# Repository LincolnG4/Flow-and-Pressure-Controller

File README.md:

# Protótipo de controle de fluxo de massa e leitura de pressão

O objetivo principal deste trabalho é desenvolver um protótipo de um sistema, composto de _hardware_, _firmware_ e _software_, para controle do fluxo e pressão de gases durante tratamento de materiais.

Os objetivos :

- Desenvolver um protótipo de um sistema de controle e alimentação de 4 _MFC_ MKS 500 _SCCM_ e leitura de pressão através de 1 Pirani APGX-M-NW16/ALI Edwards;

-  Desenvolver modos de funcionamento programados, tais como: liga/desliga de coleta sensores, pre-sets de gases comuns e alerta de erro;
- Desenvolver a placa de circuito impresso;
- Desenvolver a coleta de dados dos sensores.

## Wish list
Lista de desejos para o futuro do projeto:  
- [ ] Estudo mais detalhado dos resultados dos sinais aplicando metrologia; _`Em desenvolvimento`_
- [ ]  Sofware em Python para concatenar e gerar um grafico interativo; _`Em desenvolvimento`_
- [ ] Utilização de um hardware com Wi-Fi embutido e com mais de um núcleo, assim, permitindo multitarefas;
- [ ] Utilização de um processador de fácil integração na placa PCB;
- [ ] Otimização da programação; _`Em desenvolvimento`_
- [ ] Garantir a não utilização de um hardware genérico;
- [ ] Utilização de um roteador de internet dentro do laboratório;
- [ ] Remodelar o case para montagem por encaixe clicáveis ao invés de parafusos; _`Em desenvolvimento`_
- [ ] Função para alteração de data e hora do RTC; _`Em desenvolvimento`_

# 1. Visão Geral

 - Fonte de alimentação: 24 V ( **O módulo Step-Down aceita até 40 V de entrada, porém é necessário desmonta-lo e regular através do parafuso a saída para 7V** )
 - Sinal de saída: 0-5 V
 - Dimensões: 165,5 x 74,6 x 41 mm
 - Tela: Nextion Touch 320x240
 - Armazenamento: cartão microSD até 64 GB e 15GB em nuvem
 - Portas: 4 entradas DB9-macho, 1 entrada RJ45-femea e uma porta usb (debug)

## 1.1 Componentes

| Componente | Unidade | Preço/unidade (R$) | Total | Link | 
|--|--|--|--|--|
|Arduino Mega|1| 200,00 | 200,00  | [Compre](https://www.baudaeletronica.com.br/arduino-mega-2560-compativel-cabo-usb.html) |
| Capacitor 1uF |9| 0,23 | 2,07 | [Compre](https://www.eletrogate.com/capacitor-eletrolitico-1uf-x-50v ) |
| Conector DB9|4|3,00  | 12,00 |  [Compre](https://www.soldafria.com.br/conector-db9-macho-90-graus-solda-placa-p-1709.html) |
| Conector RJ45 |1|4,00 | 4,00  |  |
| Conector Alimentação|1| 2,50 | 2,50  | [Compre](https://www.robocore.net/conector/conector-dc-p4-femea)  |
| Fonte de alimentação 24V |1| 30,00 | 30,00 |  |
| Modulo Leitor de microSD | 1 | 12,00 | 12,00 | [Compre](https://www.eletrogate.com/modulo-micro-sd-card)  |
| Modulo LM2596 StepDown | 1 |15,00  | 15,00  | [Compre](https://www.filipeflop.com/produto/regulador-de-tensao-lm2596-conversor-dc-dc-step-down/) |
| Modulo WiFi ESP8266 |1| 20,00 | 20,00  | [Compre](https://www.eletrogate.com/modulo-wifi-serial-esp8266-esp-01) |
| Resistor 4.7k Ohms |6|0,05| 0,30 | [Compre](https://www.eletrogate.com/resistor-4k7-1-4w-10-unidades ) |
| Resistor 470 Ohms |8| 0,05 |0,40 |[Compre](https://www.eletrogate.com/resistor-4k7-1-4w-10-unidades )  |
| Resistor 220 Ohms |1| 0,05 | 0,05  |[Compre](https://www.eletrogate.com/resistor-4k7-1-4w-10-unidades ) |
| RTC 1302 | 1 | 10,00 |10,00 | [Compre](https://www.eletrogate.com/modulo-real-time-clock-ds1302) |
| Tela Nextion 320x240 |1| 120,00 |120,00  | [Compre](https://pt.aliexpress.com/item/32685352949.html?spm=a2g0o.productlist.0.0.10a12308w7t6Pf&algo_pvid=ee404ca7-f5a8-4c20-a123-40767543fb84&algo_exp_id=ee404ca7-f5a8-4c20-a123-40767543fb84-0&pdp_ext_f=%7B%22sku_id%22%3A%2260390805771%22%7D&pdp_npi=2%40dis%21BRL%21%21102.36%21%21%2133.26%21%21%402101d4a716547459631704164eff88%2160390805771%21sea)|
| Transistor BC337 |4| 0,27 | 1,08 | [Compre](https://www.eletrogate.com/ecfjb2rzm-transistor-npn-bc337)  |
| __TOTAL__ ||  |  __544,40__|  |

## 1.2 Tabela de fatores de correção dos gases

Faça o download da tabela de fatores de coreção dos gases em  [DOWNLOAD](https://github.com/LincolnG4/Flow-and-Pressure-Controller/blob/main/gasfactor.xlsx)

## 1.3 FAQ & Troubleshooting

> **A tela do produto está funcionando mas ele não retorna nenhum valor de medição**

- Certifique-se que os conectores da tela estão soldados corretamente 
- Conecte o Arduino na porta USB do seu computador e siga os passos  do tópico `3.3.1.1`
- Certifique-se que não aparecerá nenhuma mensagem de erro no monitor

# 2. Software Utilizados

| SOFTWARE        | DESCRIÇÃO|DOWNLOAD |
|----------------|-------------------------------|-------------------------------|
|`Cura3D`|Software para impressão 3D|https://ultimaker.com/software/ultimaker-cura|
|`FreeCAD 0.19`|CAD|https://www.freecadweb.org/downloads.php	|
|`Kicad 6.0`|Eletrônica e PCB |https://www.kicad.org/download/|
|`Nextion Editor`|Edição da interface LCD|https://nextion.tech/nextion-editor/|
|`Photopea`|Edição de fotos|https://photopea.com/|
|`Schematic editor`|Auto routing para trilha PCB|https://layouteditor.com/download|
|`Visual Studio Code e/ou Arduino IDE`|Edição de codigos|https://code.visualstudio.com / https://www.arduino.cc/en/software/download|

## 2.2 Links úteis 
[Basico do Arduino](https://www.if.ufrj.br/~gpenello/DisciplinasAntigas/Lab2_2018-1/GUIA_ARDUINO_v.2.pdf)
[Básico de Linguagem C++](https://www.inf.ufpr.br/ci208/NotasAula.pdf)
[Básico Cura 3D](https://3dlab.com.br/cura-3d-ultimaker/)
[FreeCAD -> SolidWorks / SolidWorks -> FreeCAD](https://forum.freecadweb.org/viewtopic.php?style=4&t=20778)

# 3. Passo a Passo de construção e instalação
## 3.1 Impressão do  case 3D

Faça o download dos arquivos para impressão 3D:
- [Gabinete](https://github.com/LincolnG4/Flow-and-Pressure-Controller/blob/main/Hardware/CAD/case_bottom-Body.stl)
- [Tampa](https://github.com/LincolnG4/Flow-and-Pressure-Controller/blob/main/Hardware/CAD/case_top-Body.stl)

Recomendações:

- Materiais: PLA ou ABS;
- Confira a [tabela de temperatura](https://3dlab.com.br/temperatura-na-impressao-3d/) para o bico para cada material;
- Configuração através do software [Cura 3D](#software-utilizados):  

## 3.2 Configurando seu ambiente de programação
 Faça o download das bibliotecas a seguir e siga o passo a passo para configuração do seu ambiente de desenvolvimento.
 
### 3.2.1 Bibliotecas Externas Utilizadas 

#### Arduino 

Versão da placa: Arduino AVR Boards 1.8.3
| SOFTWARE        | DESCRIÇÃO|DOWNLOAD |
|----------------|-------------------------------|-------------------------------|
|`ITEADLIB Arduino`|Auxiliar no controle da tela LCD|https://github.com/itead/ITEADLIB_Arduino_Nextion|
|`ArduinoRTClibrary`|Controle do modulo RTC|https://github.com/chrisfryer78/ArduinoRTClibrary|
|`Timelib`|Manipulação time string|https://github.com/PaulStoffregen/Time|
|`UnixTime`|Manipulação de timestamp|https://github.com/GyverLibs/UnixTime|
_______

#### ESP01 

Versão da placa: esp8266 2.4.3
| SOFTWARE        | DESCRIÇÃO|DOWNLOAD |
|----------------|-------------------------------|-------------------------------|
|`WiFi Manager`|Auxiliar no controle do WiFi|https://github.com/tzapu/WiFiManager|

### 3.2.2 Como instalar uma biblioteca 

 1. Abra o link para o donwload da biblioteca (ex: `https://github.com/itead/ITEADLIB_Arduino_Nextion`) e faça o download do `.ZIP`  
 
2. Abra o `Arduino IDE` e vá em `Sketch`>`Incluir biblioteca`> `Adicionar biblioteca .ZIP`  

3. Selecione a biblioteca que você fez o download no Passo 1 

### 3.2.3 Como instalar os gerenciador de placa 

#### Arduino 

1. Abra o `Arduino IDE` e clique em `Ferramentas`>`Placa`>`Gerenciador de placas`  

2. Procure pela placa `Arduino AVR Boards` e selecione a versão `1.8.3`  
_______
#### ESP01
1.Abra o `Arduino IDE` e vá em `Arquivos`>`Preferências`  
2. No campo `URLs adicionais de Gerenciadores de Placas`, insira o link  `http://arduino.esp8266.com/stable/package_esp8266com_index.json`  

3. Vá em `Ferramentas`>`Placa`>`Gerenciador de placas`  
4. Procure pela placa `esp8266 by ESP8266 community` e selecione a versão `2.4.3`  
 
## 3.3  Implementando firmware
Com todas as bibliotecas configuradas, é possível desenvolver e carregar o código para o  Arduino, Esp e Nextion.

`Faça o download desse respositório e descompacte em alguma pasta do seu computado`:

### 3.3.1 Arduino
- Abra o [`Arduino IDE`](https://github.com/LincolnG4/Flow-and-Pressure-Controller/blob/main/README.md#2Software-Utilizados) em seu computador e vá em `Arquivo` > `Abrir`
- Vá até a pasta onde voce descompactou o repositório repositório, navegue por `Flow-and-Pressure-Controller-main` > `project` > `main.ino`   
- Certifique-se que a pasta `lib` esta na mesma pasta que o `main.lib`  

- Conecte o `Arduino Mega` via porta `USB`  
- Clique em `Ferramentas` e selecione as configurações :  
  
 *obs: a porta irá variar de acordo com a porta que o Arduino foi conectado ao seu dispositivo 

- Clique no botão `Verificar`, se o IDE não retornar nenhum erro, clique no botão `Carregar`

- Se tudo ocorrer certo, o IDE ira retornar a mensagem `Carregado`

#### 3.3.1.1 Debugging Arduino
Caso você esteja desconfiado que o Arduino não está funcionando corretamente, ative a opção de debbuging:

1. Abra o `Arduino IDE` > `main.ino`
2. Pressione as teclas `Ctrl` + `F` para abrir o terminal `Localizar`
3. Preencha:

|**Campo** | **Valor** |
|--|--|
|_Localizar_ | `//Serial.` |
|_Substituir com_ | `Serial.` |

4. Clique em `Substituir todos`. Isso retira a marcação de comentário das mensagens serial de debug, ou seja, após as substituições as mensagens de rotina do arduino serão mostradas via USB

5. Carregue o código, ao fim do carregamento, desconecte o USB e conecte novamente.
6. Clique em `Ferramentas` > `Monitor Serial`
7. Agora todas as atividades do Arduino serão mostradas no monitor.

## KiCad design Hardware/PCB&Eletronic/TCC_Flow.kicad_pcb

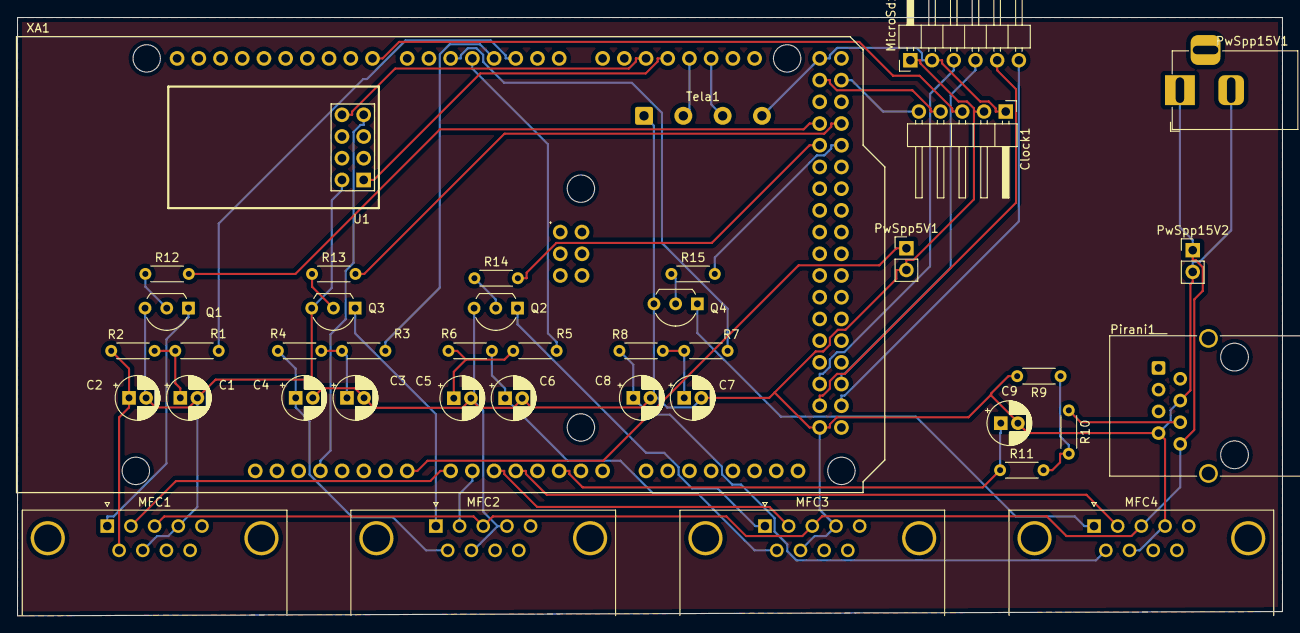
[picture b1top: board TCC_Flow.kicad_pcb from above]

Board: 2 copper layers, 148.0 x 70.0 mm, 41 parts (0 on the bottom side), 47 nets.

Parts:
C1, C2, C3, C4, C5, C6, C7, C8, C9: 1uF; CP_Radial_D5.0mm_P2.00mm
Clock1: Conn_01x05_Male; PinHeader_1x05_P2.54mm_Horizontal
MFC1, MFC2, MFC3, MFC4: Conn_01x09_Male; DSUB-9_Male_Horizontal_P2.77x2.84mm_EdgePinOffset7.70mm_Hou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
MicroSd1: Conn_01x06_Male; PinHeader_1x06_P2.54mm_Horizontal
Pirani1: Conn_01x08_Male; RJ45_Wuerth_7499010001A_Horizontal
PwSpp5V1, PwSpp15V2: Conn_01x02_Male; PinHeader_1x02_P2.54mm_Vertical
PwSpp15V1: Conn_01x02_Male; BarrelJack_Horizontal
Q1, Q2, Q3, Q4: BC337; TO-92L_Inline_Wide
R1, R2, R3, R4, R5, R6, R7, R8: 500; R_Axial_DIN0204_L3.6mm_D1.6mm_P5.08mm_Horizontal
R9, R10: 4.6K; R_Axial_DIN0204_L3.6mm_D1.6mm_P5.08mm_Horizontal
R11: 220; R_Axial_DIN0204_L3.6mm_D1.6mm_P5.08mm_Horizontal
R12, R13, R14, R15: 4.7K; R_Axial_DIN0204_L3.6mm_D1.6mm_P5.08mm_Horizontal
Tela1: Conn_01x04_Male; SolderWire-0.5sqmm_1x04_P4.6mm_D0.9mm_OD2.1mm
U1: ESP-01v090; ESP-01
XA1: Arduino_Mega2560_Shield

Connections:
unnamed: C1.1, R1.1, R2.2
unnamed: C1.2, C2.2, C3.2, C4.2, C5.2, C6.2, C7.2, C8.2, C9.2, Clock1.2, MFC1.4, MFC1.7, MFC2.4, MFC2.7, MFC3.4, MFC3.7, MFC4.4, MFC4.7, MicroSd1.1, Pirani1.4, Pirani1.7, PwSpp5V1.2, PwSpp15V1.2, PwSpp15V2.2, Q1.3 (E), Q2.3 (E), Q3.3 (E), Q4.3 (E), R9.2, Tela1.1, U1.2 (GND), XA1.GND5 (GND)
unnamed: C2.1, MFC1.6, R2.1
unnamed: C3.1, R3.1, R4.2
unnamed: C4.1, MFC2.6, R4.1
unnamed: C5.1, R5.1, R6.2
unnamed: C6.1, MFC3.6, R6.1
unnamed: C7.1, R7.1, R8.2
unnamed: C8.1, MFC4.6, R8.1
unnamed: C9.1, R11.1, XA1.A5
unnamed: Clock1.1, MicroSd1.2, Tela1.4, XA1.5V3 (5V)
unnamed: Clock1.3, XA1.D8
unnamed: Clock1.4, XA1.D22
unnamed: Clock1.5, XA1.D23
unnamed: MFC1.1, Q1.1 (C)
unnamed: MFC1.2, XA1.A0
unnamed: MFC1.3, MFC2.3, MFC3.3, MFC4.3, Pirani1.8, PwSpp15V1.1, PwSpp15V2.1
unnamed: MFC2.1, Q3.1 (C)
unnamed: MFC2.2, XA1.A1
unnamed: MFC3.1, Q2.1 (C)
unnamed: MFC3.2, XA1.A2
unnamed: MFC4.1, Q4.1 (C)
unnamed: MFC4.2, XA1.A3
unnamed: MicroSd1.3, XA1.D50
unnamed: MicroSd1.4, XA1.D51
unnamed: MicroSd1.5, XA1.D52
unnamed: MicroSd1.6, XA1.D53 (D53_SS)
unnamed: Pirani1.6, R10.1
unnamed: PwSpp5V1.1, XA1.VIN
unnamed: Q1.2 (B), R12.1
unnamed: Q2.2 (B), R14.1
unnamed: Q3.2 (B), R13.1
unnamed: Q4.2 (B), R15.1
unnamed: R1.2, XA1.D2 (D2_INT0)
unnamed: R3.2, XA1.D3 (D3_INT1)
unnamed: R5.2, XA1.D4
unnamed: R7.2, XA1.D5
unnamed: R9.1, R10.2, R11.2
unnamed: R12.2, XA1.D26
unnamed: R13.2, XA1.D27
unnamed: R14.2, XA1.D28
unnamed: R15.2, XA1.D29
unnamed: Tela1.2, XA1.D18 (D18_TX1)
unnamed: Tela1.3, XA1.D19 (D19_RX1)
unnamed: U1.1 (UTXD), XA1.D17 (D17_RX2)
unnamed: U1.7 (VCC), XA1.3V3 (3.3V)
unnamed: U1.8 (URXD), XA1.D16 (D16_TX2)

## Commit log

2021-10-31 Start commit
2021-10-31 Flow_measure.drawio
2021-10-31 Flow_old.drawio
2021-10-31 Flow_oçd.drawio
2021-10-31 flow_old.png
2021-10-31 Diagram
2021-11-02 Flow_overview.drawio
2021-11-02 Flow_over.drawio
2022-03-31 Create file
2022-03-31 main
2022-05-21 Dev Updated
2022-05-23 deploy last version mks
2022-05-23 [page2] - GFC and MFC settings deploy
2022-05-24 [main] - organizing structure of functions
2022-05-24 [main] - organizing structure of files
2022-05-24 [main] - organizing structure of folders
2022-05-24 [repo] - organize repo
2022-05-26 [main] added comments to code
2022-05-30 [main] Update comments and function MCFPWMOff moved to MFCPWMClose
2022-05-30 [main] Bux fix - Time reset checkbox off
2022-05-31 [pirani] add color changes to error range
2022-05-31 [pirani] bug fix add color changes to error range
2022-06-02 bug fix esp01
2022-06-02 [pirani] bug fix function sending old values
2022-06-03 [ESP] bug fix message int
2022-06-06 organize
2022-06-06 hardware files
2022-06-06 [LCD] update files
2022-06-06 Create tes
2022-06-06 Create f
2022-07-11 Fix Serial value
2022-07-17 [PCB] Add updated pcb and Doc
2022-09-18 Branch code without RTC module
2022-09-18 Branch code without RTC module test
2022-09-18 Branch code without RTC modul
2022-09-18 CAD top montage bottom
